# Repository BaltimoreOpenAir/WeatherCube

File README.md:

# WeatherCube
This repo provides code and schematics for the WeatherCube, an environmental monitoring platform used for the Baltimore OpenAir project. More info is on our project page at baltimoreopenair.github.io

#

# Hardware

## Circuit Boards 

### Component list:

1- The main board: It supports the microcontrollers. Its the brain of the device

2- Charging controller: provides power to the main board, charge up the battery with the solar panel

3- Lithium polymer battery: holds the power for the device

4- Analog front end board: holds the air quality sensors

5- Coin CR battery: powers the clock in case of loss of power

6- temperature sensor board: measures temperature and humidity in the tunnel

7- solar pannel: powers the unit

8- 4x air quality sensor: for N02,03,SO2 and H2S

9- 3X Molex picoblade cable assembly (2X 4 pins and 1X 5 pins): connects boards together

10- FTDI ttl/usb controller: allows to load code

11- ttl/usb ESP adapter: allows to connect the FTDI controller to load code in the ESP wifi chip

12- ttl/usb ATMEGA adapter: allows to connect the FTDI controller to load code in the ATMEGA microcontroller

## Electronic Assembly:

### Necessary equipment

1- Soldering iron

2- snips

3- box cutter

4- lead free rosin core solder of small gauge

5- a breadboard to serve as jig

6- A good multimeter for quality check

7- tweezers

9- a brush (such as a toothbrush)

10- methanol or rubbing alcohol

### Solder male header pins onto the main sensor board 

Use male 2.54mm (1/10th in) pitch headers. The headers come in 40 pins assembly, and will need to be sniped to the correct size. for this board you need 3x 7pins, 2x 2pins and 1x 1pin headers. You can use the ttl/usb adapter and/or a breadboard as jig to hold the pins in place at a right angle from the board. the pins should protrude in the front of the board and be soldered from the back. The positions of the headers are marked by yellow cirlces in the following image.

### Solder female header pins onto the Analog Front End (AFE) board
Use female 2mm pitch 2pin headers. You will need 12x 2pin headers. The pins should protrude from the front of the board and be soldered from the back. You can make a jig with 2mm male headers on a unassembled AFE PCB in order to correctly align the female headers. The pins should be scrubed with high proof methanol or other alcohol after soldering to avoid sensor bias. Resistance should be in excess of 40M Ohm between the reference and control electrode when the sensor is not mounted. The positions of the headers are marked by yellow cirlces in the following image. 

### Solder the main sensor board to the solar charging board
The main board is to be soldered with the wires coming from the charge controller. If the battery is already soldered to the charge controller, you will be soldering live wires if the black and white wire connect. This does not constitute a danger of electrocution due to the low DC voltage but may lead to burining the charge controller if the board is shorted, and is a risk of fire. Therefore, extreme caution is necessary. The recommended order for soldering is red wire (5v) then the white wire ( enable wire). At this point, it is important to check that the red and white wires do not connect in any way, and trimming the wire ends may be a good idea. You can then solder the black wire (ground). Be careful not to short the circuit accidentally with the tip of your soldering iron. This closes the circuit. The positions of the wires are marked in the following image.

### Solder the usb/ttl adapters

The usb/ttl adapter need both male and female headers of 2.54mm pitch. The male headers are suposed to be protruding on the front of both boards and the female headers on the back. You may use a soldered main board as a jig to gold the female headers in place. To snip the female headers to the correct size, first count the numbers of pins you need and pull the next pin. You can then cut the header to sizer with a box cutter and shave the plastic for esthetics. The following image displat the positions of the male headers (yellow circles) and female headers (purple circles). For this, you need 2X 6pin male headers and 4X 7pin female headers. for the female headerds of the usb/ttl ESP adapter, you will need to pull some of the pins to fit in the soldering holes.

### Plug things together
Follow the following figures to connect the differents component together. Do not forget to place the enable jumper on the main board once the code is loaded in

## Sensors 
Read the calibration codes off the sensor QR codes using any QR code reader. Save these codes for later calibration. Then, plug in the sensors clockwise from the top left in the following order: O3, H2S, SO2, and NO2.

## Code loading

The software section describes the code that need to be loaded for the project. Here we describe the hardware setup necessary to communicate with the assembled device.

1- take the jumper off the enable pin on the main board.

2- connect the usb/ttl adapters on the wifi chip and on the atmega adapter.

3- make sure the FTDI controller jumper is on 3.3V

4- connect the FTDI controller with the usb cable to the computer. make sure that the ftdi controller has the proper driver installed. This can be done on windows by running this [executable](https://cdn.sparkfun.com/assets/learn_tutorials/7/4/CDM21228_Setup.exe).

5- connect the ftdi controller on the esp adapter.

6-  Using Arduino IDE, select the right com port and select the generic esp8266 in the tool section and load the esp8266 code. Make sure to modify the code with the target wifi credentials.

7- disconnect the FTDI controller and connect it to the atmega adapter. Using Arduino IDE, select the right com port and the arduino UNO board, load the code. You may have trouble to establish connections with the atmega when loading a code more than once. Restarting the computer seem to help in that case.

8- disconnect the adapters and put back the enable jumper. your weathercube is ready to be deployed!

## Hardware Quality checks

Using a multimeter one can check all the parameters of the device to check if all the component are working nominaly.

1- Check battery power: on the charge controller board, check the voltage potential at the soldered battery wires. The voltage should be between 2.8v and 4.2V. If close to 0V, check the battery wiring connections. If higher that 0.5V but lower than 2.8V, the battery is probably damaged. If higher than 4.2V the charge controller is damaged. If higher than 2.8V but lower than 3.3V, you should connect and charge the battery before usage using the mini usb port until reaching 4.2V.

2- Solar panel check: on the charge controller board, measure the voltage between the two wires of the solar panel. This should read between 4.1 and 4.4 V when the panel is exposed to direct sunlight. If the voltage is very low, there must be a problem in the wire connection on the solar panel. It the voltage is higher, the solar panel is runing in an open circuit, which means that either the battery is full, or if it is not, that the charge controller is damaged ore the solar panel wire connection on the charge controller is not good.

3- battery charge tester on the charge controller: click on the push button on the charge controller. If the charge controller leds do not light up and the battery voltage is superior to 2.8V this means that the charge controller is damaged.

4- main board power: check the voltage between the red and black wire of the charge controller on the main board. This should read close to 5V. if not the charge controller is damaged, or the connection of the white and black wire is not good. you can then check the volatege between vcc and ground on the board. it should read 3.3v when the enable pin is jumped and 0v else. If it reads 0V when the enable pin is in, the charge board is damaged or the connection is not good. if th reads 3.3V weither or not the jumper is on the enable pin, it means that the enable pin is shorted: check for solder residues that may short the two pins.

5- AFE board checks: the resistance between the 2mm pitch pins should be checked with a good multimeter (measurs resistance up to 40Mohm at least such as [this](https://www.amazon.com/dp/B000JKMTDM/ref=psdc_15707471_t2_B0050LVFS0)). Off the trio of headers for each sensor, the top one should have a resistance higher than 40Mohm when the sesor is not pluged in while the other should display no resistance. a 40Mohm reistance would bias the result by about 20ppb, which is the resolution of the sensor we are using. If the resistance is lower than that, pluck the plastic part of the pin and clean thourouly the plastic part and the pins with methanol. reassemble when dry and check again.

6- Fan check: in normal operation the fan should be runing every 15minutes for 30 seconds. If the fan does not run, you may try to run the fan by applying a 5v potential between its ground and live wires. Make sure you respect polarity. if the fan does not spin, it might be jammed. To unjam the fan, disasemble the air tunnel and manually check for fan rotation. take out any obstruction and check for rotation again. replace fan if need be.

7- Charging operation: check the battery volatage and note it up to 4 significant numbers. Put the weathercube in full sun for few hours. Without the main board unabled the unit should charge the battery at about .05V to .2V per hour in full unobstructed sun. The unit should still charge between .04V to .15V per hours when the unit is in operation. If not, the whole power circuit (solar panel, charging board and battery) might have to be recheched or replaced.

8- Com operation: when the cube is deployed in normal operation, you should recieve wifi communication once every day or as specified. if not, you may want to check first power then wifi communication credential in that unit.

# Software 

## Arduino Installation
Step zero is to install [Arduino](https://www.arduino.cc/). Note that in Linux, you may need need to launch Arduino using sudo priveleges. 

### 1. Add the ESP8266 board to Arduino. 

Follow: https://learn.sparkfun.com/tutorials/esp8266-thing-hookup-guide/installing-the-esp8266-arduino-addon 

### 2. Verify that you have the following libraries. If not, in Arduino, click Sketch--> Include Library --> Manage Libraries and search for the following libraries. When you find the library, click on it and an install button should appear. Click on this button to install. 
- Statistic
- SoftwareSerial
- Wire
- Adafruit_ADS1015
- EEPROM
- ESP8266WiFi

### 3. Download the following libraries for the Arduino Uno and save to your default Arduino library path (~/Arduino/libraries/): 
- [LMP91000](https://github.com/LinnesLab/LMP91000)
- [ClosedCube_HDC1080](https://github.com/closedcube/ClosedCube_HDC1080_Arduino/tree/master/src)
- [Adafruit_SHT31](https://github.com/adafruit/Adafruit_SHT31)
- [LowPower](https://github.com/rocketscream/Low-Power)
Note that on github, to download individual files you right-click on "raw" in the middle right and select "save file as". The files must be located in folders of the same name. 

### 4. Download the following files/libraries for the ESP8266 : 
Download and move the following files into the `AWSArduinoSDK` directory you just created: 
- [Esp8266AWSImplementations.h](https://github.com/daniele-salvagni/aws-sdk-esp8266/tree/master/src/esp8266)
- AmazonDynamoDBClient.h(https://github.com/daniele-salvagni/aws-sdk-esp8266/tree/master/src/common)
- AWSFoundationalTypes.h(https://github.com/daniele-salvagni/aws-sdk-esp8266/tree/master/src/common)

## AWS setup 
These instructions are courtesy Daniele Salvagni at https://github.com/daniele-salvagni/aws-sdk-esp8266/ 

### 1. Create an AWS account

Create an account at https://aws.amazon.com/. Note this requires a credit card but it's possible to be on AWS' free tier. You may also qualify for educational credits. Follow along steps 1 and 2 using the instructions in http://ncar.github.io/chords/aws.html . 

Then, create a user in the IAM managment console: https://docs.aws.amazon.com/IAM/latest/UserGuide/id_users_create.html#id_users_create_console
Get your awsKeyID and awsSecKey in the last step by going to IAM--> Users--> Security credentials. . 

### 2. Set up the DynamoDB Table

You will need to set up a DynamoDB table with the same name, hash key, and range key as in the sample you are using. These values are defined as constants in the sample, i.e. `HASH_KEY_NAME` and `TABLE_NAME`.

You can follow the steps below to get the tables set up with the right values:

* Log into the [AWS Console](http://console.aws.amazon.com/) and navigate to **DynamoDB**.
* Click on the "Create Table" button.
* Enter `ESP8266AWSDemo` as the *Table Name*, `id` as the primary *Partition Key*, and `timest` as the primary *Sort Key*. Be sure to mark *id* as *String* and *timest* as *Number*.
* Just one *Read Capacity Unit* and one *Write Capacity Unit* will be more than enough for this demo. Press create with these values.
* After the table has finished creating you are good to go, your ESP will take care about populating it.

### 3. Creating `keys.h` and `keys.cpp`

You will need to create and add `keys.h` and `keys.cpp` into the `AWSArduinoSDK` directory you made. Alternatively, if you want to use different access keys for every sketch you make, just put them inside your current sketch folder. These files define the `awsKeyID` and `awsSecKey` values used by the sketch, the files may be structured as following:

```
// keys.h
#ifndef KEYS_H_
#define KEYS_H_

extern const char* awsKeyID;  // Declare these variables to
extern const char* awsSecKey; // be accessible by the sketch
extern const char* pSSID; 
extern const char* pPassword; 
extern const char* SERIAL_ID;

#endif
```

```
// keys.cpp
#include "keys.h"

const char* awsKeyID = "YOUR AWS KEY ID HERE";
const char* awsSecKey = "YOUR AWS SECRET KEY HERE";
extern const char* pSSID = "YOUR WIFI NETWORK NAME HERE"; 
extern const char* pPassword = "YOUR PASSWORD HERE"; 
extern const char* SERIAL_ID = "ID NUMBER HERE";
```

*Do not share your AWS keys with anyone, it is reccomended to create a dedicated user with restricted permissions, do not use your root account. If you accidentally push your keys online disable them immediatly from the [AWS IAM console](https://console.aws.amazon.com/iam/home)*

## Programming 
### 1.  Bootload the boards using Atmel studio (if we've given you boards, we've already done this for you)
### 2. Load the Blink example sketch onto the ATMega selecting Arduino Uno as the board 
For this step, you could use any sketch onto the ATMega that doesn't tie up the serial lines, such as reset_esp.ino.
### 3. Edit the keys.h file from AWS setup step 3
### 4. Load esp_main sketch onto the ESP8266 
### 4. Load wxcube_main sketch onto the ATMega using the Uno settings

# Data 
### Data access through AWS Console
To view your data, log in to the [AWS Console](http://console.aws.amazon.com/) and navigate to **DynamoDB**. Click on "Tables" in the left hand menu, select your table and click on "Items". To download your table, first create a filter by selecting "filter". You can select for ids or for time. Note that ids are strings and time is a number such as '20170908000015'.  Click start search. When the search is complete, click "Actions" and select  "Download as CSV". 

### Command line/Python data access
Install and configure Boto3 in Python following the [documentation](https://boto3.readthedocs.io/en/latest/guide/quickstart.html#installation). 

The following sample code can be used to retrieve one sensor's data and turn it into a Pandas dataframe with a 'datetime' index. 

```
import pandas as pd
import boto3
from boto3.dynamodb.conditions import Key, Attr
dynamodb = boto3.resource('dynamodb')
table = dynamodb.Table('BaltimoreOpenAir2017')
sel_id = 1 # change this to the sensor id you are querying 
# the following will pull any data after September 8, 2017; change to your desired date
response = table.query(KeyConditionExpression=Key('id').eq(str(sel_id)) & Key('timest').gt(20170908000015)) 
df = pd.DataFrame(response['Items'])
# clean up the dataframe
df['timest'] = [pd.to_datetime(str(date)[:-4], format = '%Y%m%d%H%M') for date in df['timest']]
# read in batteryAV to get the time
df[['something', 'HourMinute', 'MonthDay', 'AV', 'drop'] ] = df['battAV'].str.split(',').apply(pd.Series)
# key in the calibration codes, m_o3, m_no2, m_so2, m_h2s
df[['O3_avg', 'O3_std']]   = df[['O3_avg', 'O3_std']].astype(float)/ m_o3)
df[['NO2_avg', 'NO2_std']] = df[['NO2_avg', 'NO2_std']].astype(float)/m_no2)
df[['SO2_avg', 'SO2_std']] = df[['SO2_avg', 'SO2_std']].astype(float)/m_so2)
df[['H2S_avg', 'H2S_std']] = df[['H2S_avg', 'H2S_std']].astype(float)/m_h2s)

# set up time index 
date_index = []
for date in df[['MonthDay', 'HourMinute']].values : 
    try: 
        if date[0] == '32767' : 
            date_index.append(np.nan)
        elif date[0] == '0' : 
            date_index.append(np.nan)
        else:
            date_index.append(pd.to_datetime('2017' +date[0]+date[1], format = '%Y%m%d%H%M'))
    except ValueError:  
        date_index.append(np.nan)
df['date_index'] = date_index
```

For an implementation of the code & a proposed calibration technique, see (https://github.com/BaltimoreOpenAir/BOAFieldEvaluation/blob/master/MDE_Beltsville_Analysis.ipynb).

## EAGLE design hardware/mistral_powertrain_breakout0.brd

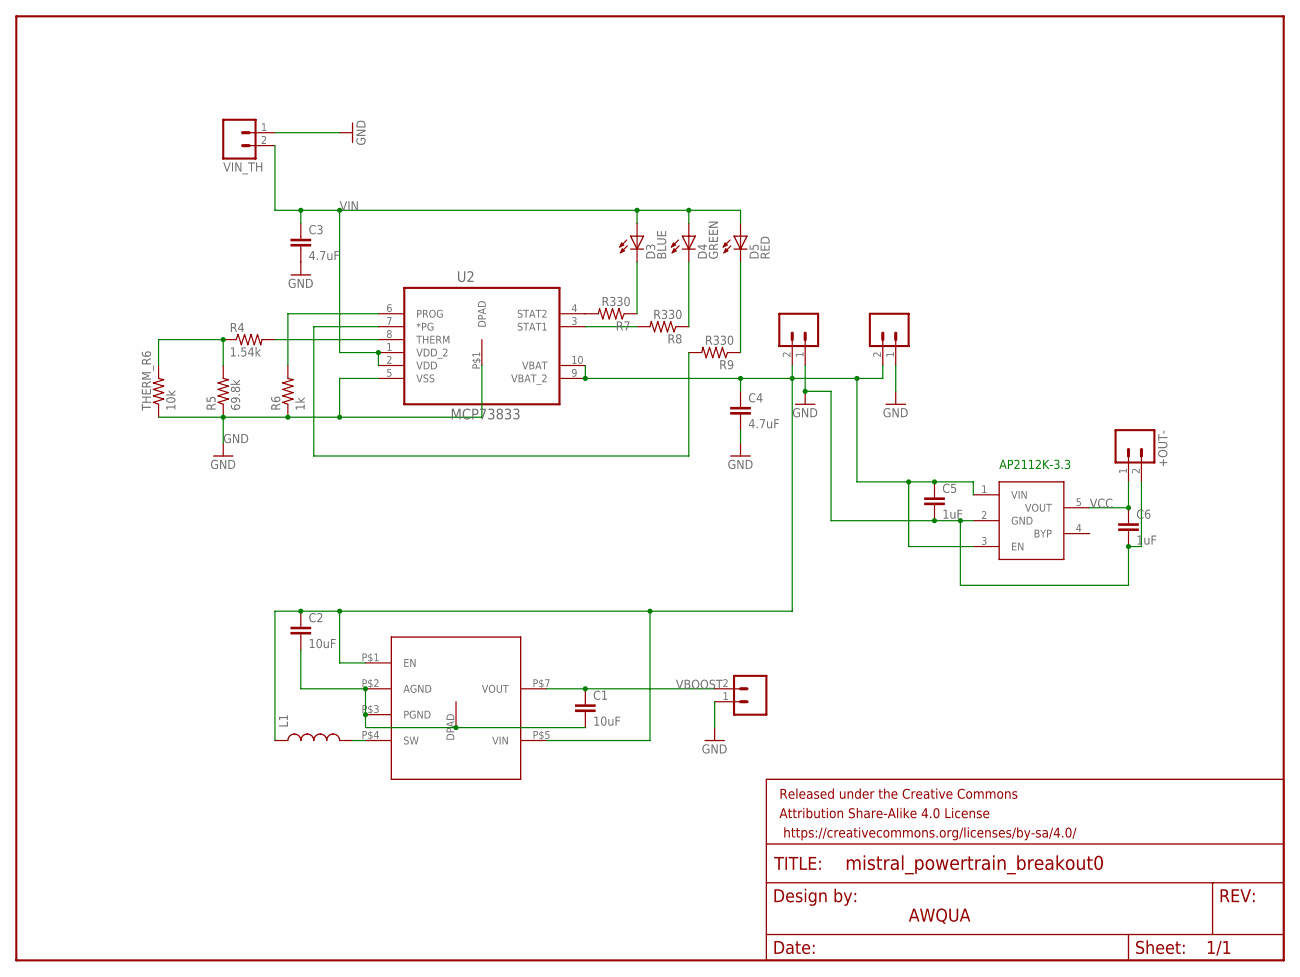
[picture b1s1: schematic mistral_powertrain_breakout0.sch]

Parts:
+OUT-: M02PTH; 1X02
C1, C2: 10uF; 0402-CAP
C3, C4: 4.7uF; 0402-CAP
C5, C6: 1uF; 0603-CAP
D3: BLUE; LED-0603
D4: GREEN; LED-0603
D5: RED; LED-0603
FRAME1: FRAME-LETTER; CREATIVE_COMMONS
JMP, JMP1: M02PTH; 1X02
JP7: LiPo Battery; JST-2-SMD
L1: INDUCTOR0805; 0805
R4: 1.54k; 0402-RES
R5: 69.8k; 0402-RES
R6: 1k; 0402-RES
R7, R8, R9: R330; 0402-RES
THERM_R6: 10k; 0402-RES
U2: MCP73833; SOP50P490X110-10N
U$1: DIO6605B
U$2: LP2985
VIN_TH: M02PTH; 1X02

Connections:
GND: +OUT-.2, C3.2, C4.2, C5.2, C6.2, JMP.1, JMP1.1, JP7.1, R5.1, R6.1, THERM_R6.1, U2.5 (VSS), U2.P$1 (DPAD), U$2.2 (GND), VIN_TH.1
unnamed: C1.2, C2.2, U$1.DPAD (DGND), U$1.P$2 (AGND), U$1.P$3 (PGND)
unnamed: L1.2, U$1.P$4 (SW)
unnamed: R4.2, U2.8 (THERM)
unnamed: R4.1, R5.2, THERM_R6.2
unnamed: R6.2, U2.6 (PROG)
unnamed: R7.2, U2.4 (STAT2)
unnamed: D3.C, R7.1
unnamed: R8.2, U2.3 (STAT1)
unnamed: D4.C, R8.1
unnamed: D5.C, R9.1
unnamed: R9.2, U2.7 (*PG)
VBAT: C2.1, C4.1, C5.1, JMP.2, JP7.2, L1.1, U2.9 (VBAT_2), U2.10 (VBAT), U$1.P$1 (EN), U$1.P$5 (VIN), U$2.1 (VIN), U$2.3 (EN)
VBOOST: C1.1, JMP1.2, U$1.P$7 (VOUT)
VCC: +OUT-.1, C6.1, U$2.5 (VOUT)
VIN: C3.1, D3.A, D4.A, D5.A, U2.1 (VDD_2), U2.2 (VDD), VIN_TH.2

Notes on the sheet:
AWQUA
AP2112K-3.3

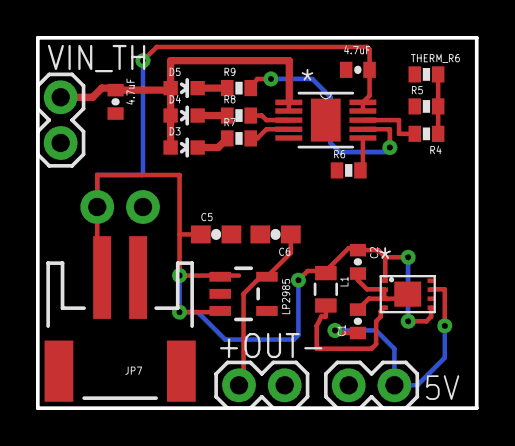
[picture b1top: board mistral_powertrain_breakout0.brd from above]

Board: 2 copper layers, 24.4 x 20.6 mm, 26 parts (1 on the bottom side), 16 nets.

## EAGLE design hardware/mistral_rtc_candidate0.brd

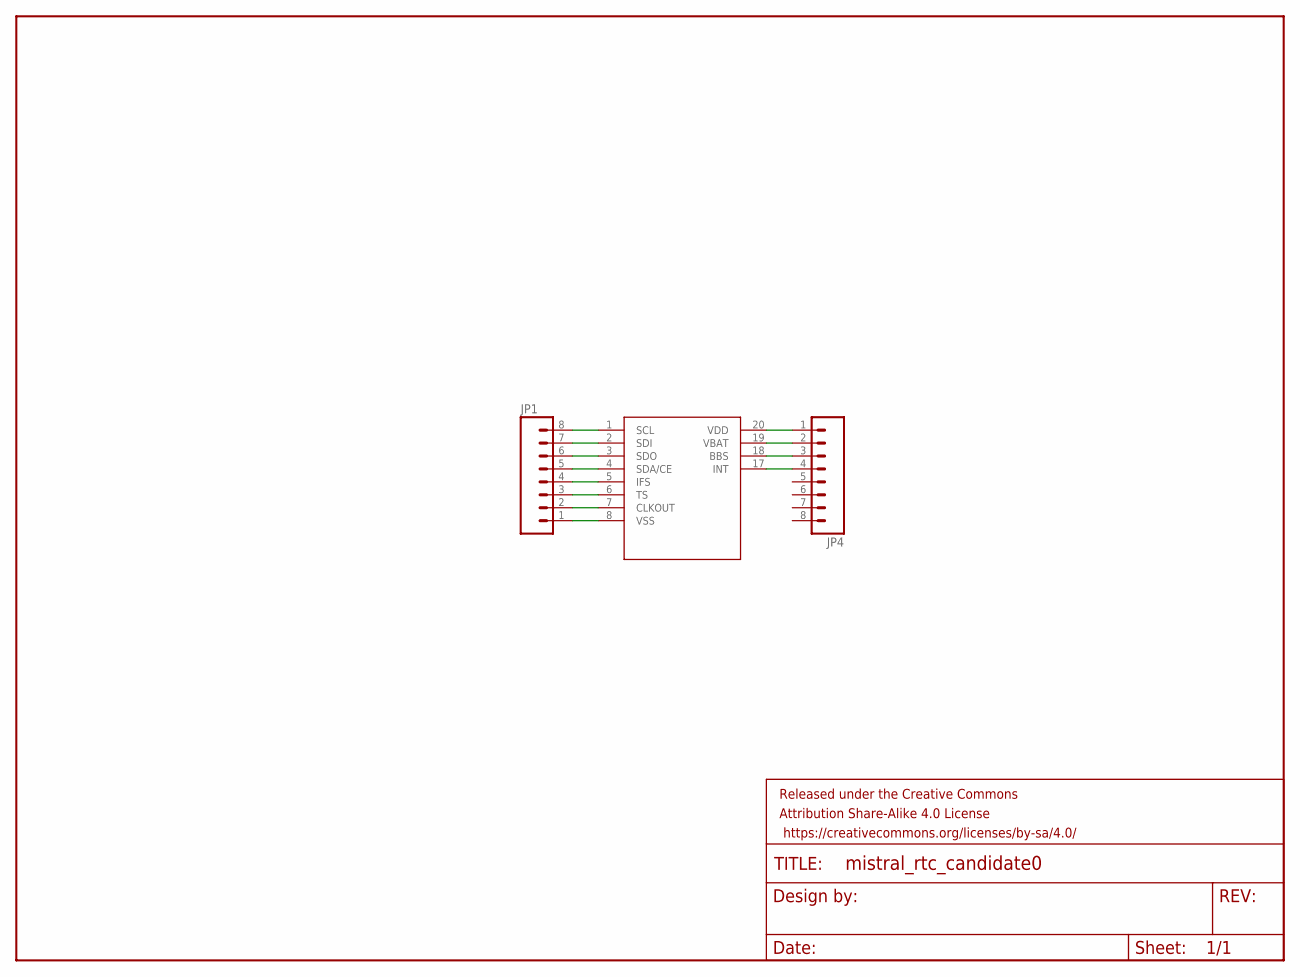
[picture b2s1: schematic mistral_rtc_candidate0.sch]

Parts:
FRAME1: FRAME-LETTER; CREATIVE_COMMONS
JP1, JP4: M08SILK_FEMALE_PTH; 1X08
U$1: PCF2129

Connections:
unnamed: JP1.1, U$1.8 (VSS)
unnamed: JP1.2, U$1.7 (CLKOUT)
unnamed: JP1.3, U$1.6 (TS)
unnamed: JP1.4, U$1.5 (IFS)
unnamed: JP1.5, U$1.4 (SDA/CE)
unnamed: JP1.6, U$1.3 (SDO)
unnamed: JP1.7, U$1.2 (SDI)
unnamed: JP1.8, U$1.1 (SCL)
unnamed: JP4.1, U$1.20 (VDD)
unnamed: JP4.2, U$1.19 (VBAT)
unnamed: JP4.3, U$1.18 (BBS)
unnamed: JP4.4, U$1.17 (INT)

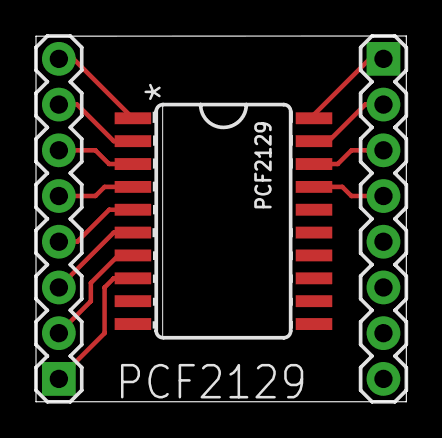
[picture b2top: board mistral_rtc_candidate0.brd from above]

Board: 2 copper layers, 20.6 x 20.3 mm, 4 parts (0 on the bottom side), 12 nets.

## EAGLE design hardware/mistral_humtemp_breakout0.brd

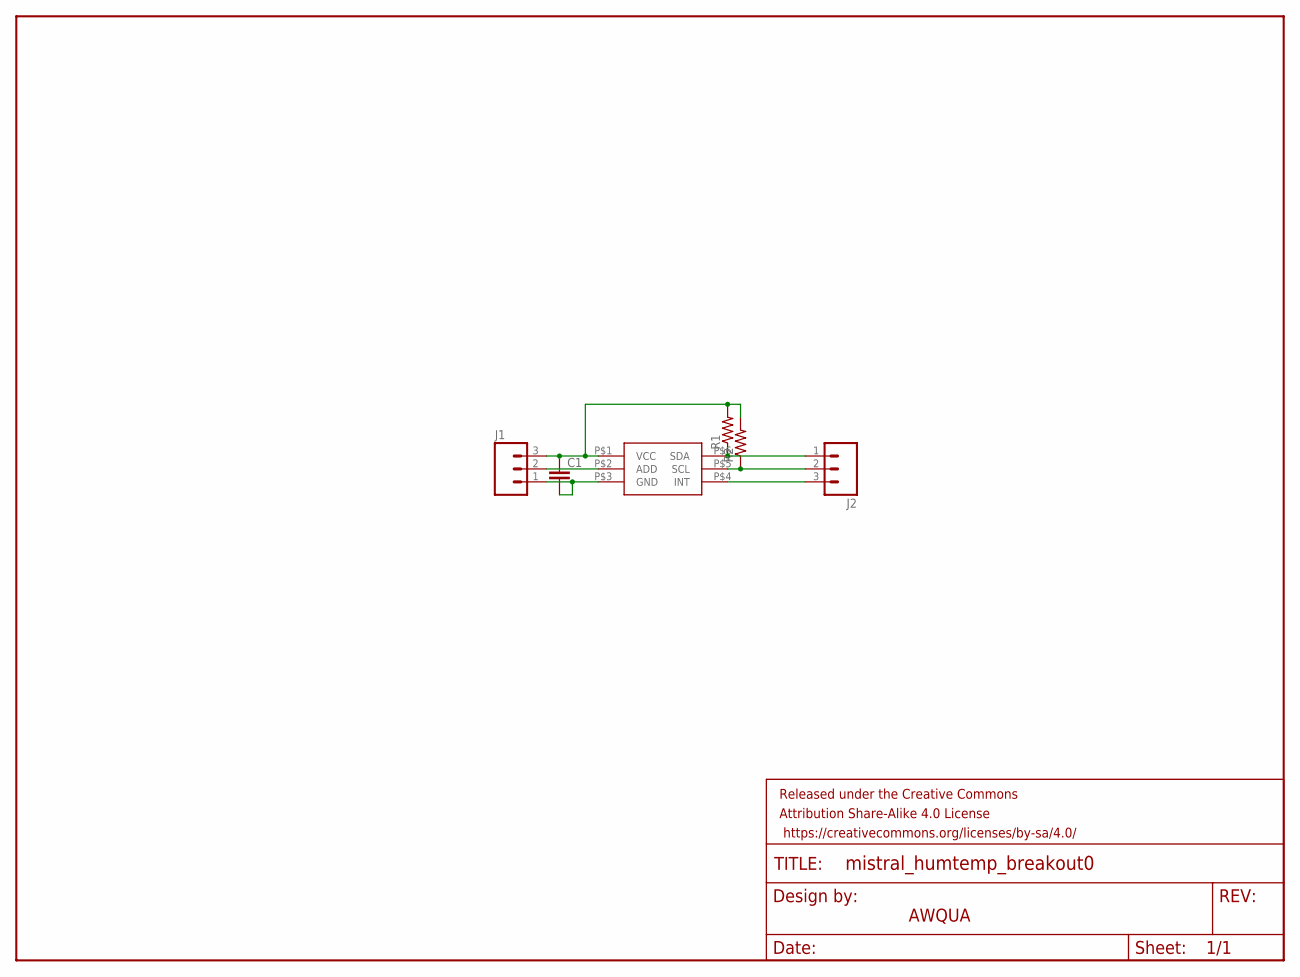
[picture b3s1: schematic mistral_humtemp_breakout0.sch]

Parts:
C1: CAP0603-CAP; 0603-CAP
FRAME1: FRAME-LETTER; CREATIVE_COMMONS
J1, J2: M03PTH; 1X03
R1, R2: RESISTOR0603-RES; 0603-RES
U$1: HDC2010

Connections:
ADD: J1.2, U$1.P$2 (ADD)
GND: C1.2, J1.1, U$1.P$3 (GND)
INT: J2.3, U$1.P$4 (INT)
SCL: J2.2, R2.1, U$1.P$5 (SCL)
SDA: J2.1, R1.1, U$1.P$6 (SDA)
VCC: C1.1, J1.3, R1.2, R2.2, U$1.P$1 (VCC)

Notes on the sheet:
AWQUA

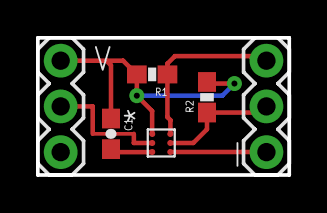
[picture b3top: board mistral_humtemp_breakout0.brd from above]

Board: 2 copper layers, 14.0 x 7.6 mm, 7 parts (0 on the bottom side), 6 nets.

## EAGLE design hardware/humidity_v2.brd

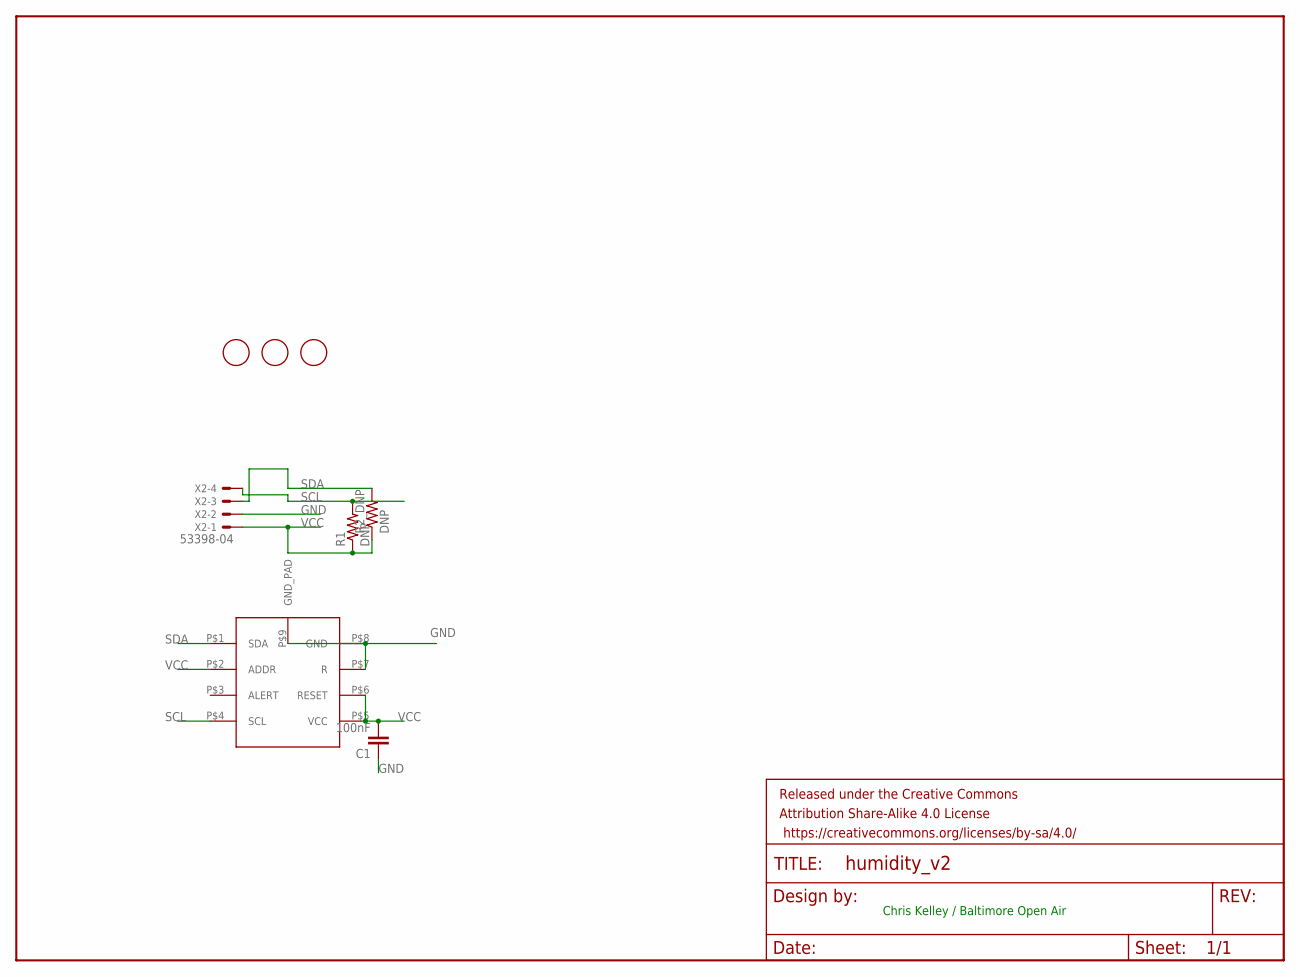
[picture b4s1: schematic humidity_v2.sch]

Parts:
C1: 100nF; 0603-CAP
FRAME1: FRAME-LETTER; CREATIVE_COMMONS
R1, R2_DNP: DNP; 0603-RES
U$1: SHT31-D
U$3, U$6, U$7: FIDUCIAL; FIDUCIAL_1MM
X2: 53398-04

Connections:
GND: C1.1, U$1.P$7 (R), U$1.P$8 (GND), U$1.P$9 (GND_PAD), X2.2
SCL: R1.2, U$1.P$4 (SCL), X2.4
SDA: R2_DNP.2, U$1.P$1 (SDA), X2.3
VCC: C1.2, R1.1, R2_DNP.1, U$1.P$2 (ADDR), U$1.P$5 (VCC), U$1.P$6 (RESET), X2.1

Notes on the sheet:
Chris Kelley / Baltimore Open Air

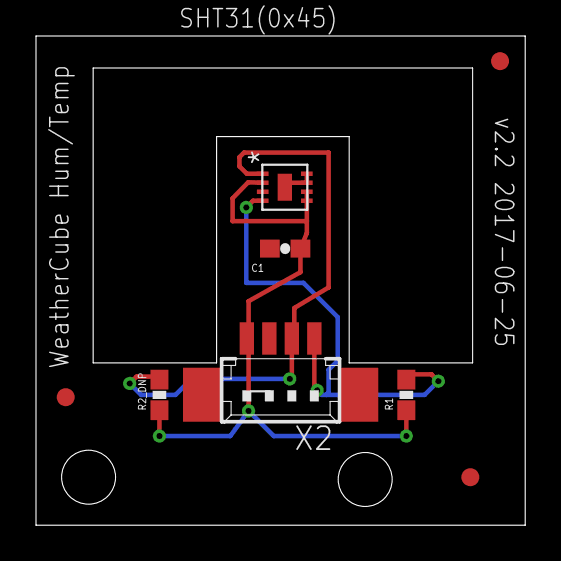
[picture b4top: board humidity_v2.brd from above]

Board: 2 copper layers, 27.2 x 27.2 mm, 9 parts (0 on the bottom side), 4 nets.

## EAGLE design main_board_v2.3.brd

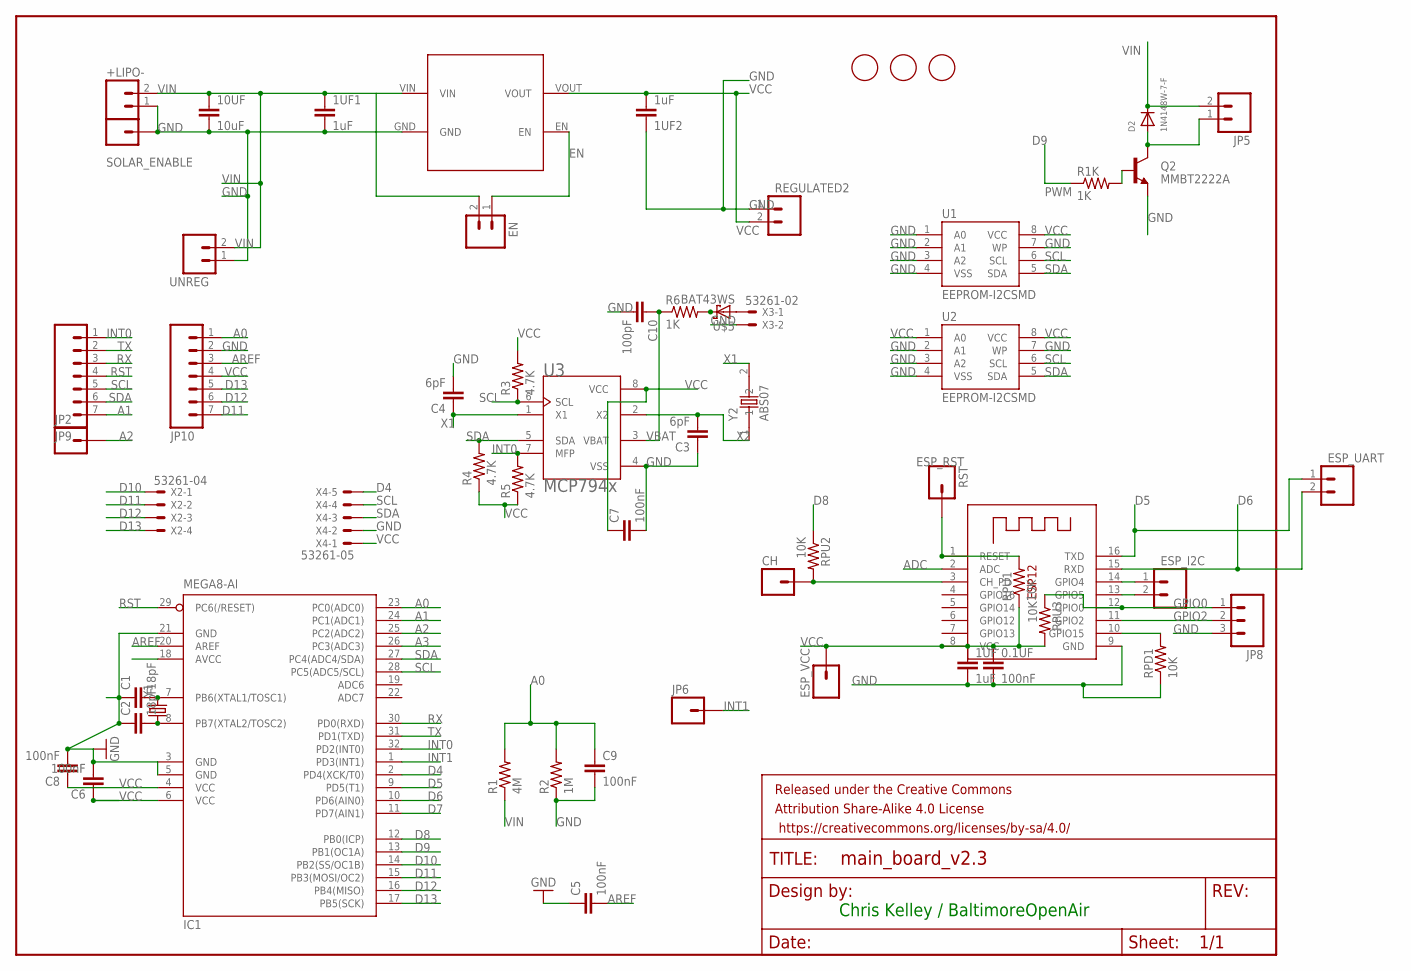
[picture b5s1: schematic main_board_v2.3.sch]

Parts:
0.1UF: 100nF; 0603-CAP
1UF, 1UF1, 1UF2: 1uF; 0603-CAP
10UF: 10uF; 0805
+LIPO-: M02PTH; 1X02
C1, C2: 18pF; 0603-CAP
C3, C4: 6pF; 0603-CAP
C5, C6, C7, C8, C9: 100nF; 0603-CAP
C10: 100pF; 0603-CAP
CH: M01PTH; 1X01
D2: 1N4148W-7-F; SOD-123
EN: M02PTH; 1X02
ESP_I2C: M02PTH; 1X02
ESP_UART: M02PTH; 1X02
ESP_VCC: M01PTH; 1X01
FRAME1: FRAME-LETTER; CREATIVE_COMMONS
IC1: MEGA8-AI; TQFP32-08
JP2, JP6: M01PTH; 1X01
JP5: M02-JST-2MM-SMT; JST-2-SMD
JP8: M03PTH; 1X03
JP9, JP10: M07; 1X07
Q2: MMBT2222A; SOT23-3
R1: 4M; 0603-RES
R1K, R6: 1K; 0603-RES
R2: 1M; 0603-RES
R3, R4, R5: 4.7K; 0603-RES
REGULATED2: M02PTH; 1X02
RPD1: 10K; 0603-RES
RPU1, RPU2, RPU3: 10K; 0603-RES
RST: M01PTH; 1X01
SOLAR_ENABLE: M01PTH; 1X01
U1, U2: EEPROM-I2CSMD; SO08
U3: MCP794x; SOIC127P600X175-8N
U$3, U$6, U$7: FIDUCIAL; FIDUCIAL_1MM
U$4: AP2112K; AP2112K-SOT23-5
U$5: BAT43WS
UNREG: M02PTH; 1X02
X1: ESP-12
X2: 53261-04
X3: 53261-02
X4: 53261-05
Y1: CRYSTAL5X3; CRYSTAL-SMD-5X3
Y2: ABS07; XTAL320X150X90

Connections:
A0: C9.1, IC1.23 (PC0(ADC0)), JP10.1, R1.2, R2.2
A1: IC1.24 (PC1(ADC1)), JP9.7
A2: IC1.25 (PC2(ADC2)), JP2.1
A3: IC1.26 (PC3(ADC3))
ADC: X1.2 (ADC)
AREF: C5.2, IC1.20 (AREF), JP10.3
CH_PD: CH.1, RPU2.2, X1.3 (CH_PD)
D4: IC1.2 (PD4(XCK/T0)), X4.5
D5: ESP_UART.1, IC1.9 (PD5(T1)), X1.16 (TXD)
D6: ESP_UART.2, IC1.10 (PD6(AIN0)), X1.15 (RXD)
D7: IC1.11 (PD7(AIN1))
D8: IC1.12 (PB0(ICP)), RPU2.1
D9: IC1.13 (PB1(OC1A)), R1K.1
D10: IC1.14 (PB2(SS/OC1B)), X2.1
D11: IC1.15 (PB3(MOSI/OC2)), JP10.7, X2.2
D12: IC1.16 (PB4(MISO)), JP10.6, X2.3
D13: IC1.17 (PB5(SCK)), JP10.5, X2.4
EN: EN.1, U$4.EN
ESP_RST: RPU1.2, RST.1, X1.1 (RESET)
GND: 0.1UF.2, 1UF.2, 1UF1.2, 1UF2.1, 10UF.2, +LIPO-.1, C1.1, C2.1, C3.1, C4.2, C5.1, C6.2, C7.2, C8.2, C9.2, C10.2, IC1.3 (GND), IC1.5 (GND), IC1.21 (GND), JP8.3, JP10.2, Q2.2 (E), R2.1, REGULATED2.1, RPD1.1, SOLAR_ENABLE.1, U1.1 (A0), U1.2 (A1), U1.3 (A2), U1.4 (VSS), U1.7 (WP), U2.2 (A1), U2.3 (A2), U2.4 (VSS), U2.7 (WP), U3.4 (VSS), U$4.GND, UNREG.1, X1.9 (GND), X3.2, X4.2
GPIO0: JP8.1, RPU3.1, X1.12 (GPIO0)
GPIO2: JP8.2, X1.11 (GPIO2)
GPIO15: RPD1.2, X1.10 (GPIO15)
INT0: IC1.32 (PD2(INT0)), JP9.1, R5.2, U3.7 (MFP)
INT1: IC1.1 (PD3(INT1)), JP6.1
unnamed: D2.A, JP5.1 (2), Q2.3 (C)
unnamed: U$5.PIN1 (C), X3.1
unnamed: ESP_I2C.1, X1.14 (GPIO4)
unnamed: R6.2, U$5.PIN2 (A)
unnamed: ESP_I2C.2, X1.13 (GPIO5)
PWM: Q2.1 (B), R1K.2
Q1: C2.2, IC1.8 (PB7(XTAL2/TOSC2)), Y1.1
Q2: C1.2, IC1.7 (PB6(XTAL1/TOSC1)), Y1.3 (2)
RST: IC1.29 (PC6(/RESET)), JP9.4
RX: IC1.30 (PD0(RXD)), JP9.3
SCL: IC1.28 (PC5(ADC5/SCL)), JP9.5, R3.1, U1.6 (SCL), U2.6 (SCL), U3.6 (SCL), X4.4
SDA: IC1.27 (PC4(ADC4/SDA)), JP9.6, R4.2, U1.5 (SDA), U2.5 (SDA), U3.5 (SDA), X4.3
TX: IC1.31 (PD1(TXD)), JP9.2
VBAT: C10.1, R6.1, U3.3 (VBAT)
VCC: 0.1UF.1, 1UF.1, 1UF2.2, C6.1, C7.1, C8.1, ESP_VCC.1, IC1.4 (VCC), IC1.6 (VCC), IC1.18 (AVCC), JP10.4, R3.2, R4.1, R5.1, REGULATED2.2, RPU1.1, RPU3.2, U1.8 (VCC), U2.1 (A0), U2.8 (VCC), U3.8 (VCC), U$4.VOUT, X1.8 (VCC), X4.1
VIN: 1UF1.1, 10UF.1, +LIPO-.2, D2.C, EN.2, JP5.2 (1), R1.1, U$4.VIN, UNREG.2
X1: C4.1, U3.1 (X1), Y2.2
X2: C3.2, U3.2 (X2), Y2.1

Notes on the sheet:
Chris Kelley / BaltimoreOpenAir

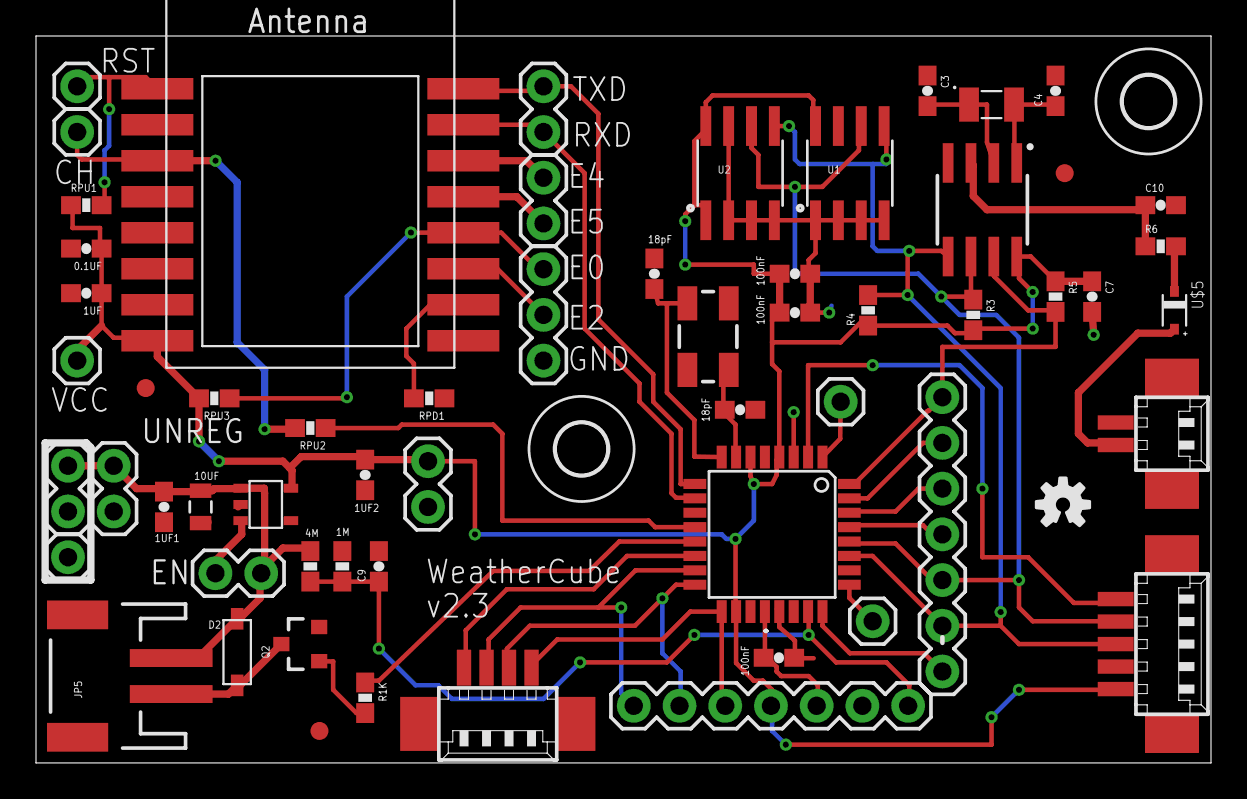
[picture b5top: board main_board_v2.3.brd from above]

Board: 2 copper layers, 65.3 x 40.4 mm, 64 parts (1 on the bottom side), 40 nets.

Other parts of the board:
U$1, U$9: 2,8
U$2, U$8: OSHW-LOGO-S

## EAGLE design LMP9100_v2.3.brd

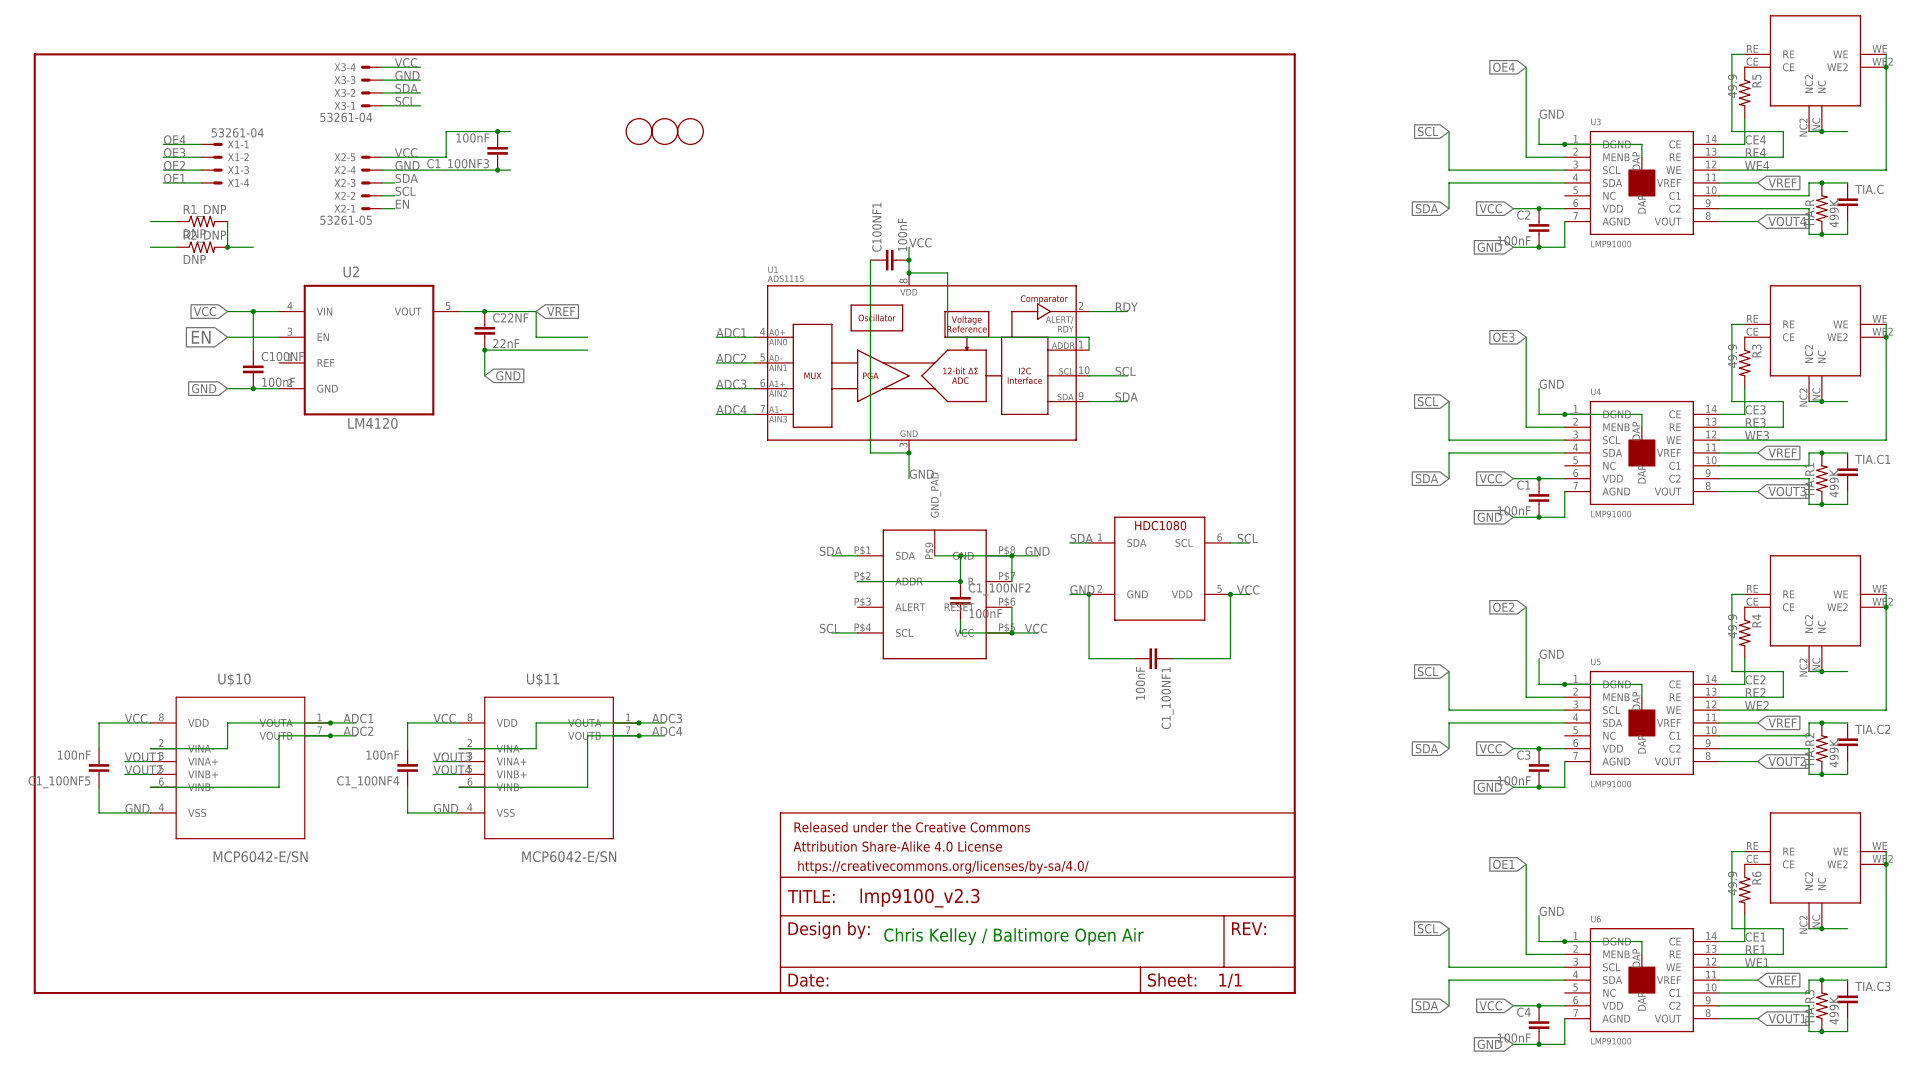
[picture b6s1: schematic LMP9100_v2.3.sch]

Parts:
C1, C1_100NF1, C1_100NF2, C1_100NF3, C1_100NF4, C1_100NF5, C2, C3, C4, C100NF, C100NF1: 100nF; 0603-CAP
C22NF: 22nF; 0603-CAP
FRAME1: FRAME-LETTER; CREATIVE_COMMONS
R1_DNP, R2_DNP: DNP; 0603-RES
R3, R4, R5, R6: 49.9; 0603-RES
TIA.C, TIA.C1, TIA.C2, TIA.C3: CAP0603-CAP; 0603-CAP
TIA.R, TIA.R1, TIA.R2, TIA.R3: 499K; 0603-RES
U1: ADS1115; MSOP10
U2: LM4120; SOT95P284X122-5N
U3, U4, U5, U6: LMP91000
U$1, U$6, U$7: FIDUCIAL; FIDUCIAL_1MM
U$2: SHT31-D
U$3: HDC1080; WSON-6-PAD
U$4, U$5, U$8, U$9: SPEC-SENSOR
U$10, U$11: MCP6042-E/SN; SOIC127P600X175-8N
X1, X3: 53261-04
X2: 53261-05

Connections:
ADC1: U1.4 (AIN0), U$10.1 (VOUTA), U$10.2 (VINA-)
ADC2: U1.5 (AIN1), U$10.6 (VINB-), U$10.7 (VOUTB)
ADC3: U1.6 (AIN2), U$11.1 (VOUTA), U$11.2 (VINA-)
ADC4: U1.7 (AIN3), U$11.6 (VINB-), U$11.7 (VOUTB)
CE1: R6.2, U6.14 (CE)
CE2: R4.2, U5.14 (CE)
CE3: R3.2, U4.14 (CE)
CE4: R5.2, U3.14 (CE)
EN: U2.3 (EN), X2.1
GND: C1.2, C1_100NF1.2, C1_100NF2.1, C1_100NF3.1, C1_100NF4.1, C1_100NF5.1, C2.2, C3.2, C4.2, C22NF.2, C100NF.2, C100NF1.1, U1.3 (VSS), U2.2 (GND), U3.1 (DGND), U3.7 (AGND), U3.DAP, U4.1 (DGND), U4.7 (AGND), U4.DAP, U5.1 (DGND), U5.7 (AGND), U5.DAP, U6.1 (DGND), U6.7 (AGND), U6.DAP, U$2.P$2 (ADDR), U$2.P$7 (R), U$2.P$8 (GND), U$2.P$9 (GND_PAD), U$3.2 (GND), U$4.NC, U$4.NC2, U$5.NC, U$5.NC2, U$8.NC, U$8.NC2, U$9.NC, U$9.NC2, U$10.4 (VSS), U$11.4 (VSS), X2.4, X3.3
unnamed: R5.1, U$4.CE
unnamed: R3.1, U$5.CE
unnamed: R4.1, U$8.CE
unnamed: R6.1, U$9.CE
OE1: U6.2 (MENB), X1.4
OE2: U5.2 (MENB), X1.3
OE3: U4.2 (MENB), X1.2
OE4: U3.2 (MENB), X1.1
RDY: U1.2 (ALERT/RDY)
RE1: U6.13 (RE), U$9.RE
RE2: U5.13 (RE), U$8.RE
RE3: U4.13 (RE), U$5.RE
RE4: U3.13 (RE), U$4.RE
SCL: R1_DNP.1, U1.10 (SCL), U3.3 (SCL), U4.3 (SCL), U5.3 (SCL), U6.3 (SCL), U$2.P$4 (SCL), U$3.6 (SCL), X2.2, X3.1
SDA: R2_DNP.1, U1.9 (SDA), U3.4 (SDA), U4.4 (SDA), U5.4 (SDA), U6.4 (SDA), U$2.P$1 (SDA), U$3.1 (SDA), X2.3, X3.2
TIA1: TIA.C.1, TIA.R.2, U3.10 (C1)
TIA2: TIA.C.2, TIA.R.1, U3.9 (C2)
TIA3: TIA.C1.1, TIA.R1.2, U4.10 (C1)
TIA4: TIA.C1.2, TIA.R1.1, U4.9 (C2)
TIA5: TIA.C2.1, TIA.R2.2, U5.10 (C1)
TIA6: TIA.C2.2, TIA.R2.1, U5.9 (C2)
TIA7: TIA.C3.1, TIA.R3.2, U6.10 (C1)
TIA8: TIA.C3.2, TIA.R3.1, U6.9 (C2)
VCC: C1.1, C1_100NF1.1, C1_100NF2.2, C1_100NF3.2, C1_100NF4.2, C1_100NF5.2, C2.1, C3.1, C4.1, C100NF.1, C100NF1.2, R1_DNP.2, R2_DNP.2, U1.1 (ADDR), U1.8 (VDD), U2.4 (VIN), U3.6 (VDD), U4.6 (VDD), U5.6 (VDD), U6.6 (VDD), U$2.P$5 (VCC), U$2.P$6 (RESET), U$3.5 (VDD), U$10.8 (VDD), U$11.8 (VDD), X2.5, X3.4
VOUT1: U6.8 (VOUT), U$10.3 (VINA+)
VOUT2: U5.8 (VOUT), U$10.5 (VINB+)
VOUT3: U4.8 (VOUT), U$11.3 (VINA+)
VOUT4: U3.8 (VOUT), U$11.5 (VINB+)
VREF: C22NF.1, U2.5 (VOUT), U3.11 (VREF), U4.11 (VREF), U5.11 (VREF), U6.11 (VREF)
WE1: U6.12 (WE), U$9.WE, U$9.WE2
WE2: U5.12 (WE), U$8.WE, U$8.WE2
WE3: U4.12 (WE), U$5.WE, U$5.WE2
WE4: U3.12 (WE), U$4.WE, U$4.WE2

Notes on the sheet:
Chris Kelley / Baltimore Open Air

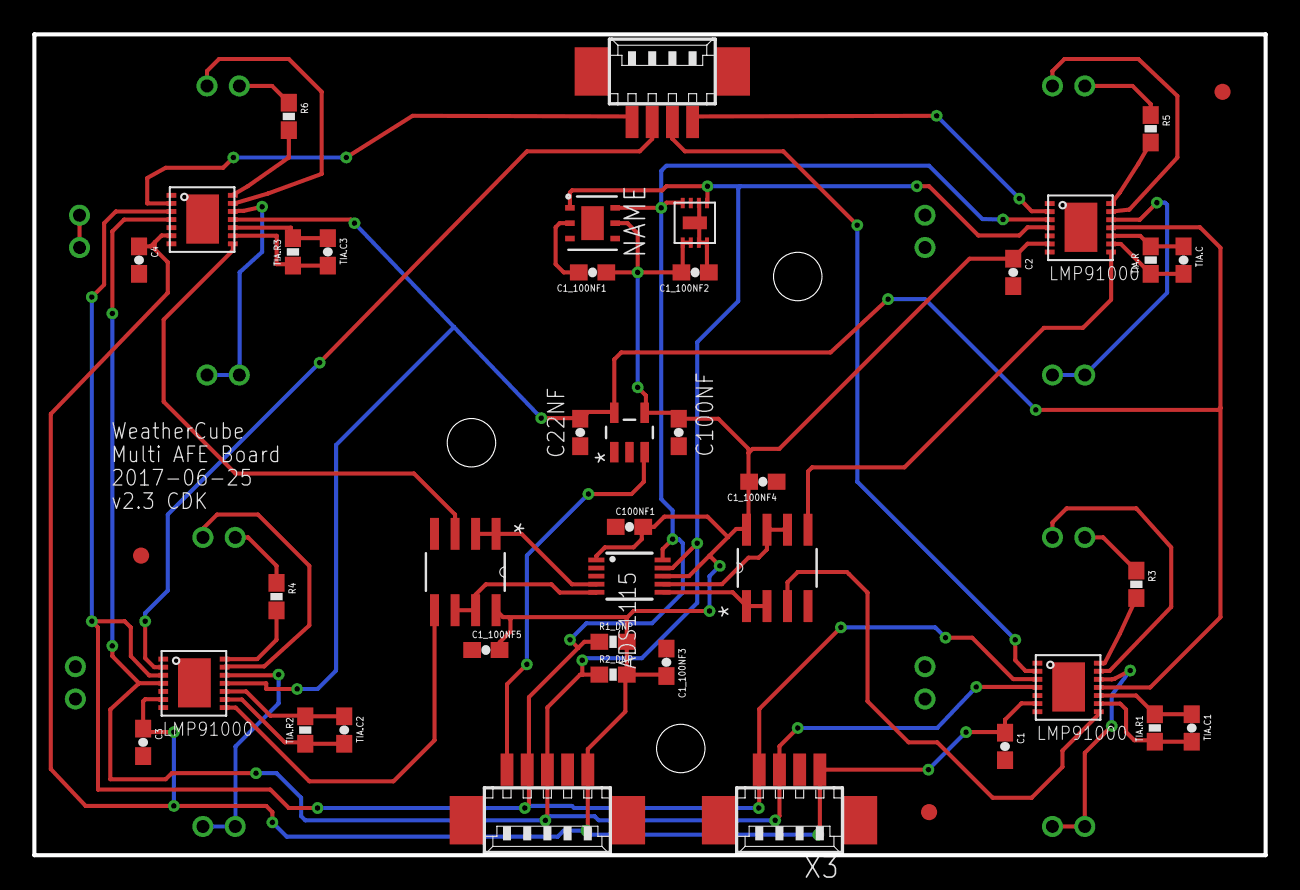
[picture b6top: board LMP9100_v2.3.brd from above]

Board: 2 copper layers, 76.2 x 50.8 mm, 47 parts (0 on the bottom side), 42 nets.

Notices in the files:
parts and their libraries:
SparkFun-Passives: Licensing: Creative Commons ShareAlike 4.0 International - https://creativecommons.org/licenses/by-sa/4.0
SparkFun-Aesthetics: Released under the Creative Commons Attribution Share-Alike 4.0 License
SparkFun-Aesthetics: https://creativecommons.org/licenses/by-sa/4.0
